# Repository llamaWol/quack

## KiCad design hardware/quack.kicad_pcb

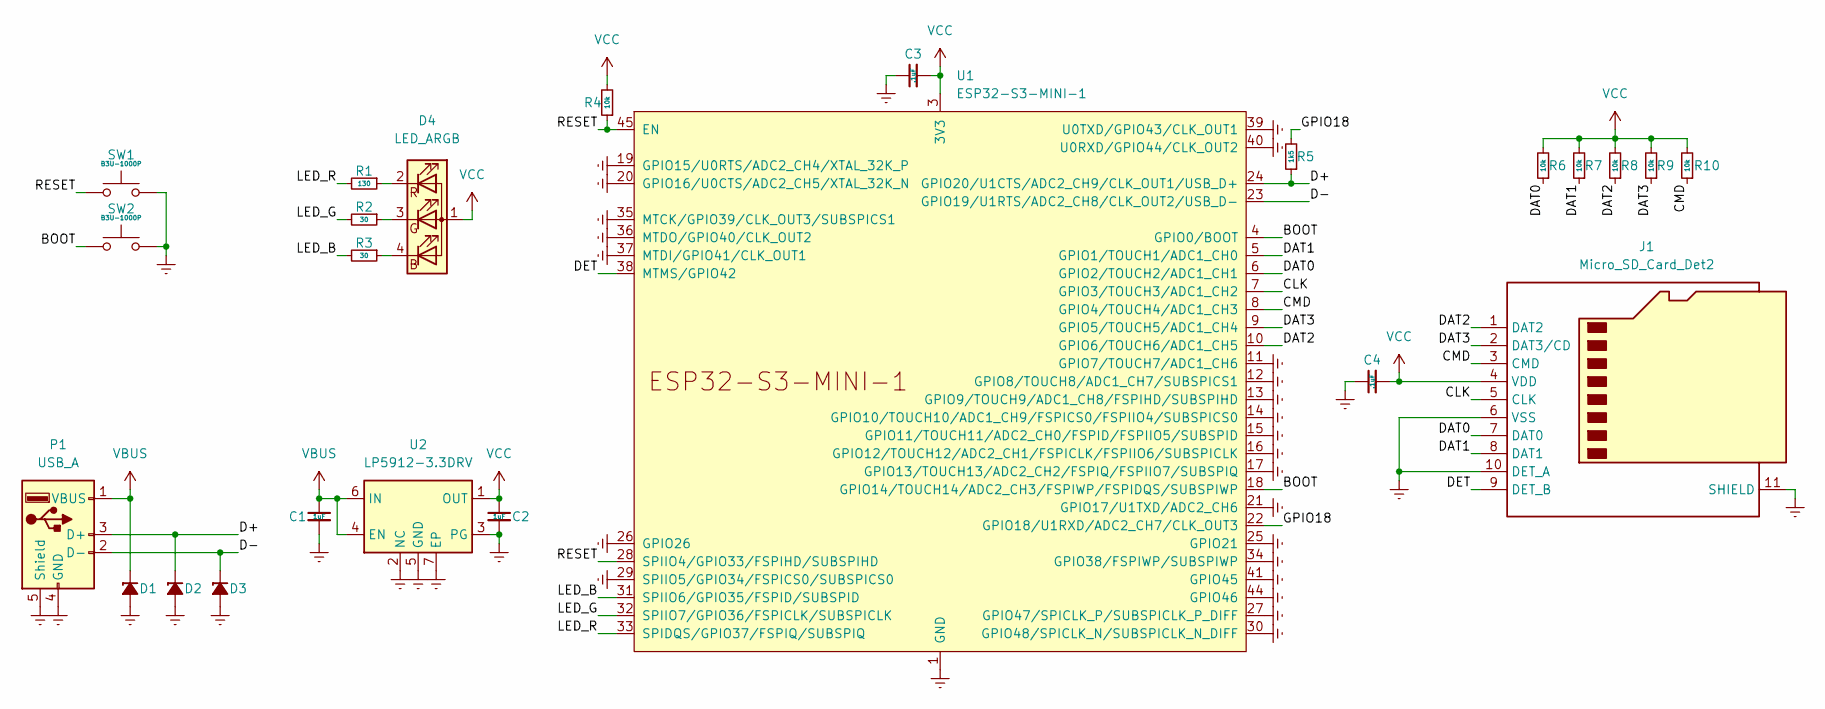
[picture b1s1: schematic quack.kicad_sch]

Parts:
C1, C2: 1uF; C_0402_1005Metric
C3, C4: .1uF; C_0402_1005Metric
D1, D2, D3: D_0402_1005Metric
D4: LED_ARGB; LED_Wurth_150044M155260
J1: Micro_SD_Card_Det2; microSD_HC_Molex_104031-0811
P1: USB_A; USB_A_Molex_48037-2200_Horizontal
R1: 130; R_0402_1005Metric
R2, R3: 30; R_0402_1005Metric
R4, R6, R7, R8, R9, R10: 10k; R_0402_1005Metric
R5: 1k5; R_0402_1005Metric
SW1, SW2: B3U-1000P; SW_SPST_B3U-1000P
U1: ESP32-S3-MINI-1
U2: LP5912-3.3DRV; WSON-6-1EP_2x2mm_P0.65mm_EP1x1.6mm_ThermalVias

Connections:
/BOOT: SW2.1, U1.4 (GPIO0/BOOT), U1.18 (GPIO14/TOUCH14/ADC2_CH3/FSPIWP/FSPIDQS/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)
/CLK: J1.5 (CLK), U1.7 (GPIO3/TOUCH3/ADC1_CH2)
/CMD: J1.3 (CMD), R10.1, U1.8 (GPIO4/TOUCH4/ADC1_CH3)
/D+: D2.1 (K), P1.3 (D+), R5.1, U1.24 (GPIO20/U1CTS/ADC2_CH9/CLK_OUT1/USB_D+)
/D-: D3.1 (K), P1.2 (D-), U1.23 (GPIO19/U1RTS/ADC2_CH8/CLK_OUT2/USB_D-)
/DAT0: J1.7 (DAT0), R6.1, U1.6 (GPIO2/TOUCH2/ADC1_CH1)
/DAT1: J1.8 (DAT1), R7.1, U1.5 (GPIO1/TOUCH1/ADC1_CH0)
/DAT2: J1.1 (DAT2), R8.1, U1.10 (GPIO6/TOUCH6/ADC1_CH5)
/DAT3: J1.2 (DAT3/CD), R9.1, U1.9 (GPIO5/TOUCH5/ADC1_CH4)
/DET: J1.9 (DET_B), U1.38 (MTMS/GPIO42)
/GPIO18: R5.2, U1.22 (GPIO18/U1RXD/ADC2_CH7/CLK_OUT3)
/LED_B: R3.2, U1.31 (SPIIO6/GPIO35/FSPID/SUBSPID)
/LED_G: R2.2, U1.32 (SPIIO7/GPIO36/FSPICLK/SUBSPICLK)
/LED_R: R1.2, U1.33 (SPIDQS/GPIO37/FSPIQ/SUBSPIQ)
/RESET: R4.1, SW1.1, U1.28 (SPIIO4/GPIO33/FSPIHD/SUBSPIHD), U1.45 (EN)
Earth: C1.2, C2.2, C3.1, C4.1, D1.2 (A), D2.2 (A), D3.2 (A), J1.6 (VSS), J1.10 (DET_A), J1.11 (SHIELD), P1.4 (GND), P1.5 (Shield), SW1.2, SW2.2, U1.1 (GND), U1.2 (GND), U1.11 (GPIO7/TOUCH7/ADC1_CH6), U1.12 (GPIO8/TOUCH8/ADC1_CH7/SUBSPICS1), U1.13 (GPIO9/TOUCH9/ADC1_CH8/FSPIHD/SUBSPIHD), U1.14 (GPIO10/TOUCH10/ADC1_CH9/FSPICS0/FSPIIO4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), U1.15 (GPIO11/TOUCH11/ADC2_CH0/FSPID/FSPIIO5/S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), U1.16 (GPIO12/TOUCH12/ADC2_CH1/FSPICLK/FSPIIO6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), U1.17 (GPIO13/TOUCH13/ADC2_CH2/FSPIQ/FSPIIO7/S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), U1.19 (GPIO15/U0RTS/ADC2_CH4/XTAL_32K_P), U1.20 (GPIO16/U0CTS/ADC2_CH5/XTAL_32K_N), U1.21 (GPIO17/U1TXD/ADC2_CH6), U1.25 (GPIO21), U1.26 (GPIO26), U1.27 (GPIO47/SPICLK_P/SUBSPICLK_P_DIFF), U1.29 (SPIIO5/GPIO34/FSPICS0/SUBSPICS0), U1.30 (GPIO48/SPICLK_N/SUBSPICLK_N_DIFF), U1.34 (GPIO38/FSPIWP/SUBSPIWP), U1.35 (MTCK/GPIO39/CLK_OUT3/SUBSPICS1), U1.36 (MTDO/GPIO40/CLK_OUT2), U1.37 (MTDI/GPIO41/CLK_OUT1), U1.39 (U0TXD/GPIO43/CLK_OUT1), U1.40 (U0RXD/GPIO44/CLK_OUT2), U1.41 (GPIO45), U1.42 (GND), U1.43 (GND), U1.44 (GPIO46), U1.46 (GND), U1.47 (GND), U1.48 (GND), U1.49 (GND), U1.50 (GND), U1.51 (GND), U1.52 (GND), U1.53 (GND), U1.54 (GND), U1.55 (GND), U1.56 (GND), U1.57 (GND), U1.58 (GND), U1.59 (GND), U1.60 (GND), U1.61 (GND), U1.62 (GND), U1.63 (GND), U1.64 (GND), U1.65 (GND), U2.2 (NC), U2.3 (PG), U2.5 (GND), U2.7 (EP)
unnamed: D4.4 (BK), R3.1
unnamed: D4.3 (GK), R2.1
unnamed: D4.2 (RK), R1.1
VBUS: C1.1, D1.1 (K), P1.1 (VBUS), U2.4 (EN), U2.6 (IN)
VCC: C2.1, C3.2, C4.2, D4.1 (A), J1.4 (VDD), R4.2, R6.2, R7.2, R8.2, R9.2, R10.2, U1.3 (3V3), U2.1 (OUT)

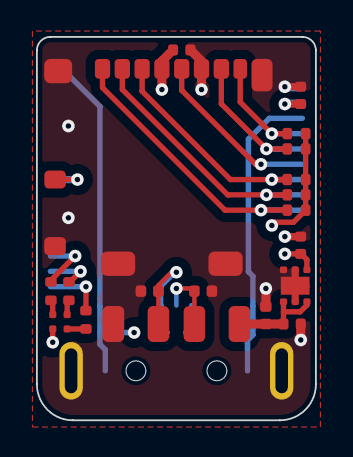
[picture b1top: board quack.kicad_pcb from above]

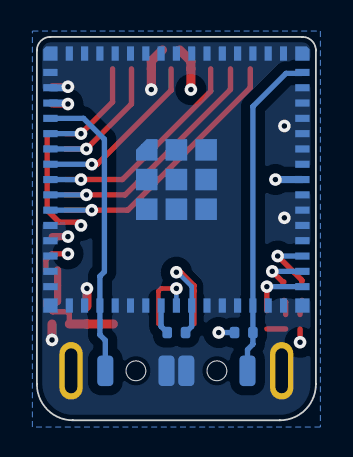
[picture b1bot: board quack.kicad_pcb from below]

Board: 4 copper layers, 15.5 x 21.3 mm, 24 parts (5 on the bottom side), 21 nets.

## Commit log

2024-03-27 Add pcb & schematic files
